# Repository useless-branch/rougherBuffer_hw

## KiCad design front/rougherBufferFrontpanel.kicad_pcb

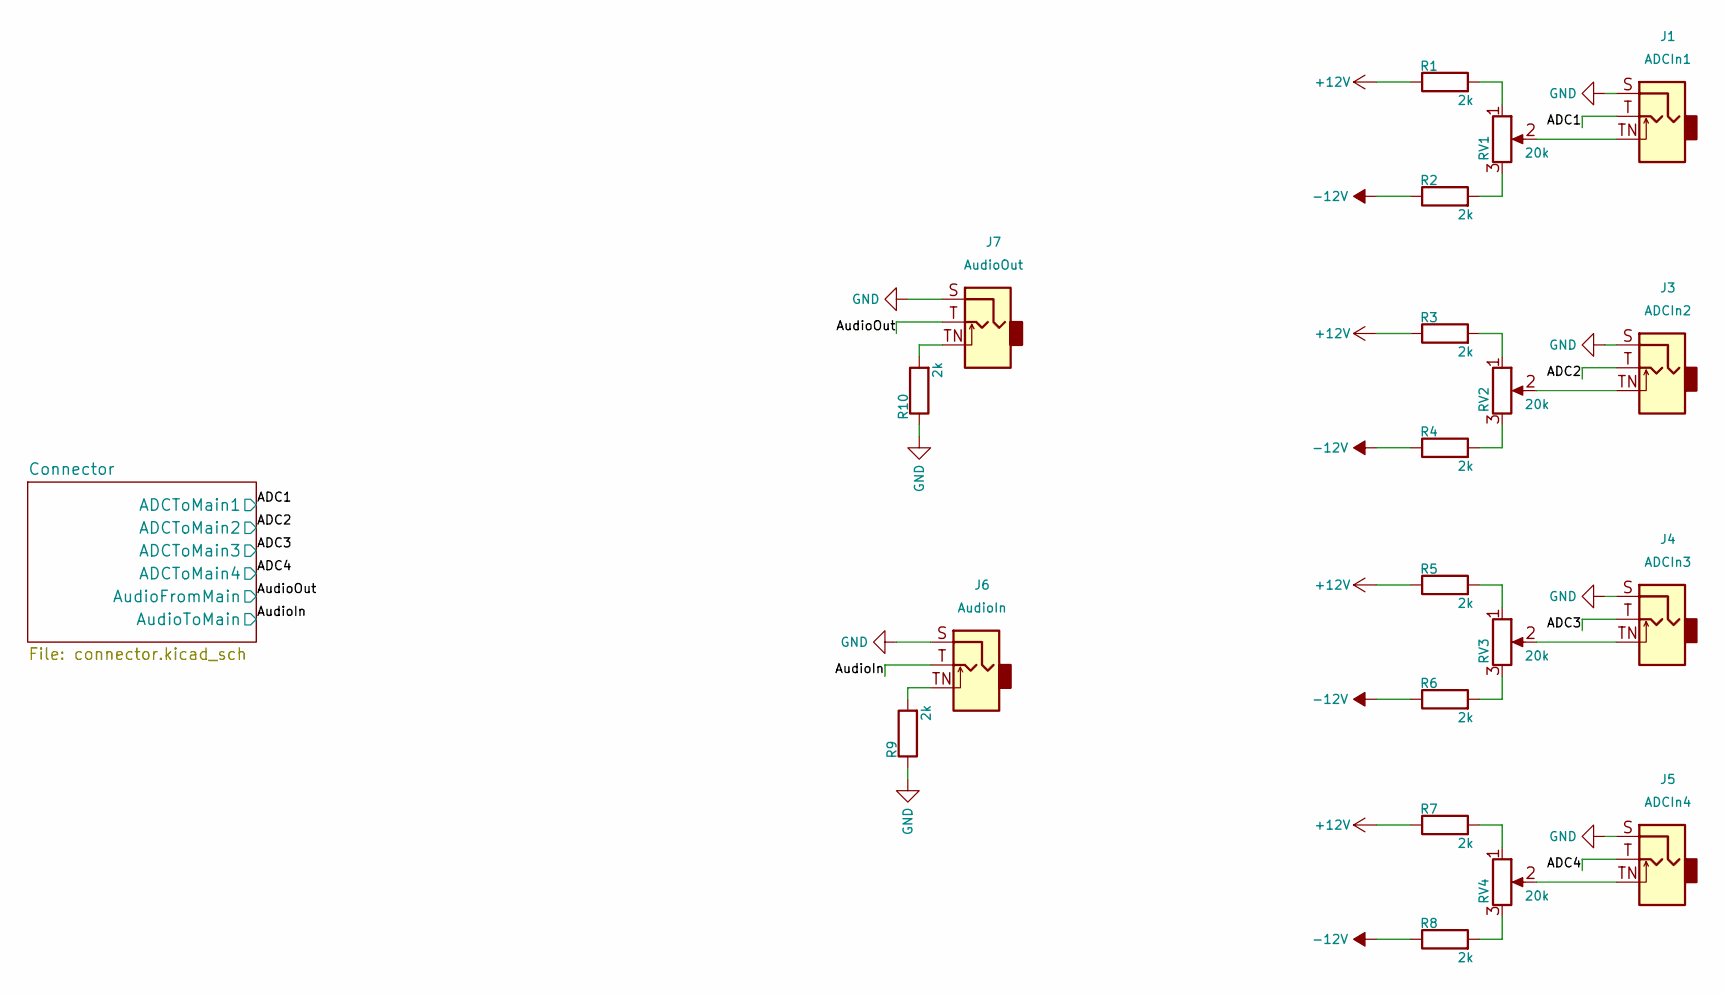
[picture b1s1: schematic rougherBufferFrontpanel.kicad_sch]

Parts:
J1: ADCIn1; Jack_3.5mm_QingPu_WQP-PJ398SM_Vertical_CircularHoles
J3: ADCIn2; Jack_3.5mm_QingPu_WQP-PJ398SM_Vertical_CircularHoles
J4: ADCIn3; Jack_3.5mm_QingPu_WQP-PJ398SM_Vertical_CircularHoles
J5: ADCIn4; Jack_3.5mm_QingPu_WQP-PJ398SM_Vertical_CircularHoles
J6: AudioIn; Jack_3.5mm_QingPu_WQP-PJ398SM_Vertical_CircularHoles
J7: AudioOut; Jack_3.5mm_QingPu_WQP-PJ398SM_Vertical_CircularHoles
R1, R2, R3, R4, R5, R6, R7, R8, R9, R10: 2k; R_0603_1608Metric
RV1, RV2, RV3, RV4: 20k; Potentiometer_Alpha_RD901F-40-00D_Single_Vertical

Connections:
+12V: R1.1, R3.1, R5.1, R7.1; also elsewhere on the board
-12V: R2.1, R4.1, R6.1, R8.1; also elsewhere on the board
/ADC1: J1.T; also elsewhere on the board
/ADC2: J3.T; also elsewhere on the board
/ADC3: J4.T; also elsewhere on the board
/ADC4: J5.T; also elsewhere on the board
/AudioIn: J6.T; also elsewhere on the board
/AudioOut: J7.T; also elsewhere on the board
GND: J1.S, J3.S, J4.S, J5.S, J6.S, J7.S, R9.1, R10.1; also elsewhere on the board
unnamed: J1.TN, RV1.2
unnamed: J3.TN, RV2.2
unnamed: J4.TN, RV3.2
unnamed: J5.TN, RV4.2
unnamed: J6.TN, R9.2
unnamed: J7.TN, R10.2
unnamed: R1.2, RV1.1
unnamed: R2.2, RV1.3
unnamed: R3.2, RV2.1
unnamed: R4.2, RV2.3
unnamed: R5.2, RV3.1
unnamed: R6.2, RV3.3
unnamed: R7.2, RV4.1
unnamed: R8.2, RV4.3

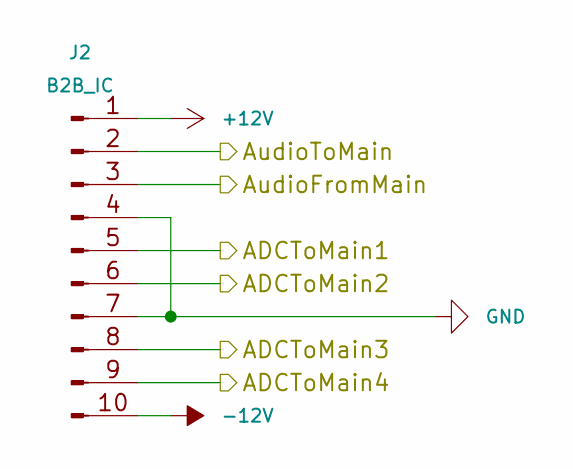
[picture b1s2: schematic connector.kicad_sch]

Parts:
J2: B2B_IC; PinHeader_1x10_P2.54mm_Vertical

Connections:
+12V: J2.1; also elsewhere on the board
-12V: J2.10; also elsewhere on the board
/ADC1: J2.5; also elsewhere on the board
/ADC2: J2.6; also elsewhere on the board
/ADC3: J2.8; also elsewhere on the board
/ADC4: J2.9; also elsewhere on the board
/AudioIn: J2.2; also elsewhere on the board
/AudioOut: J2.3; also elsewhere on the board
GND: J2.4, J2.7; also elsewhere on the board

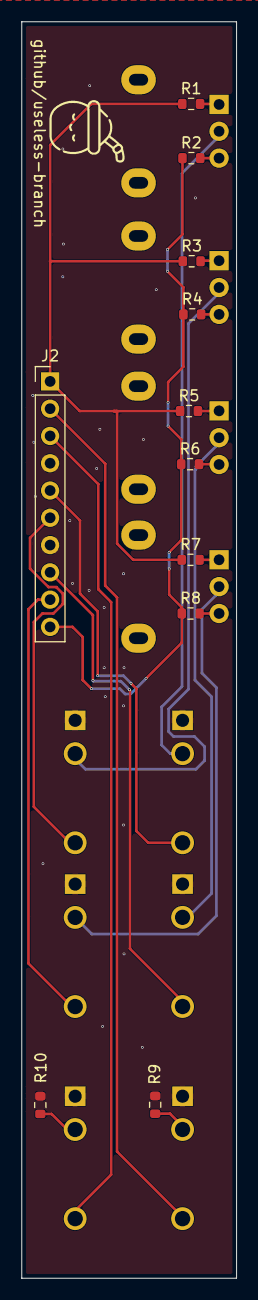
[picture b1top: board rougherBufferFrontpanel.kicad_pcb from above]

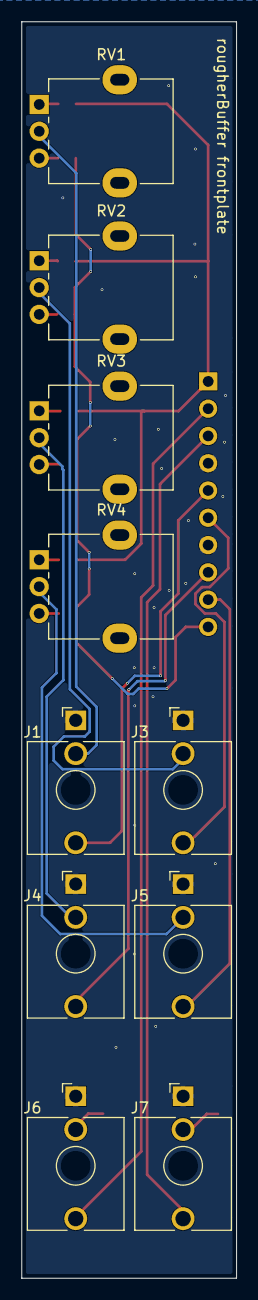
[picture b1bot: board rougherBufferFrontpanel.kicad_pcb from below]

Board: 2 copper layers, 20.0 x 117.0 mm, 21 parts (10 on the bottom side), 23 nets.

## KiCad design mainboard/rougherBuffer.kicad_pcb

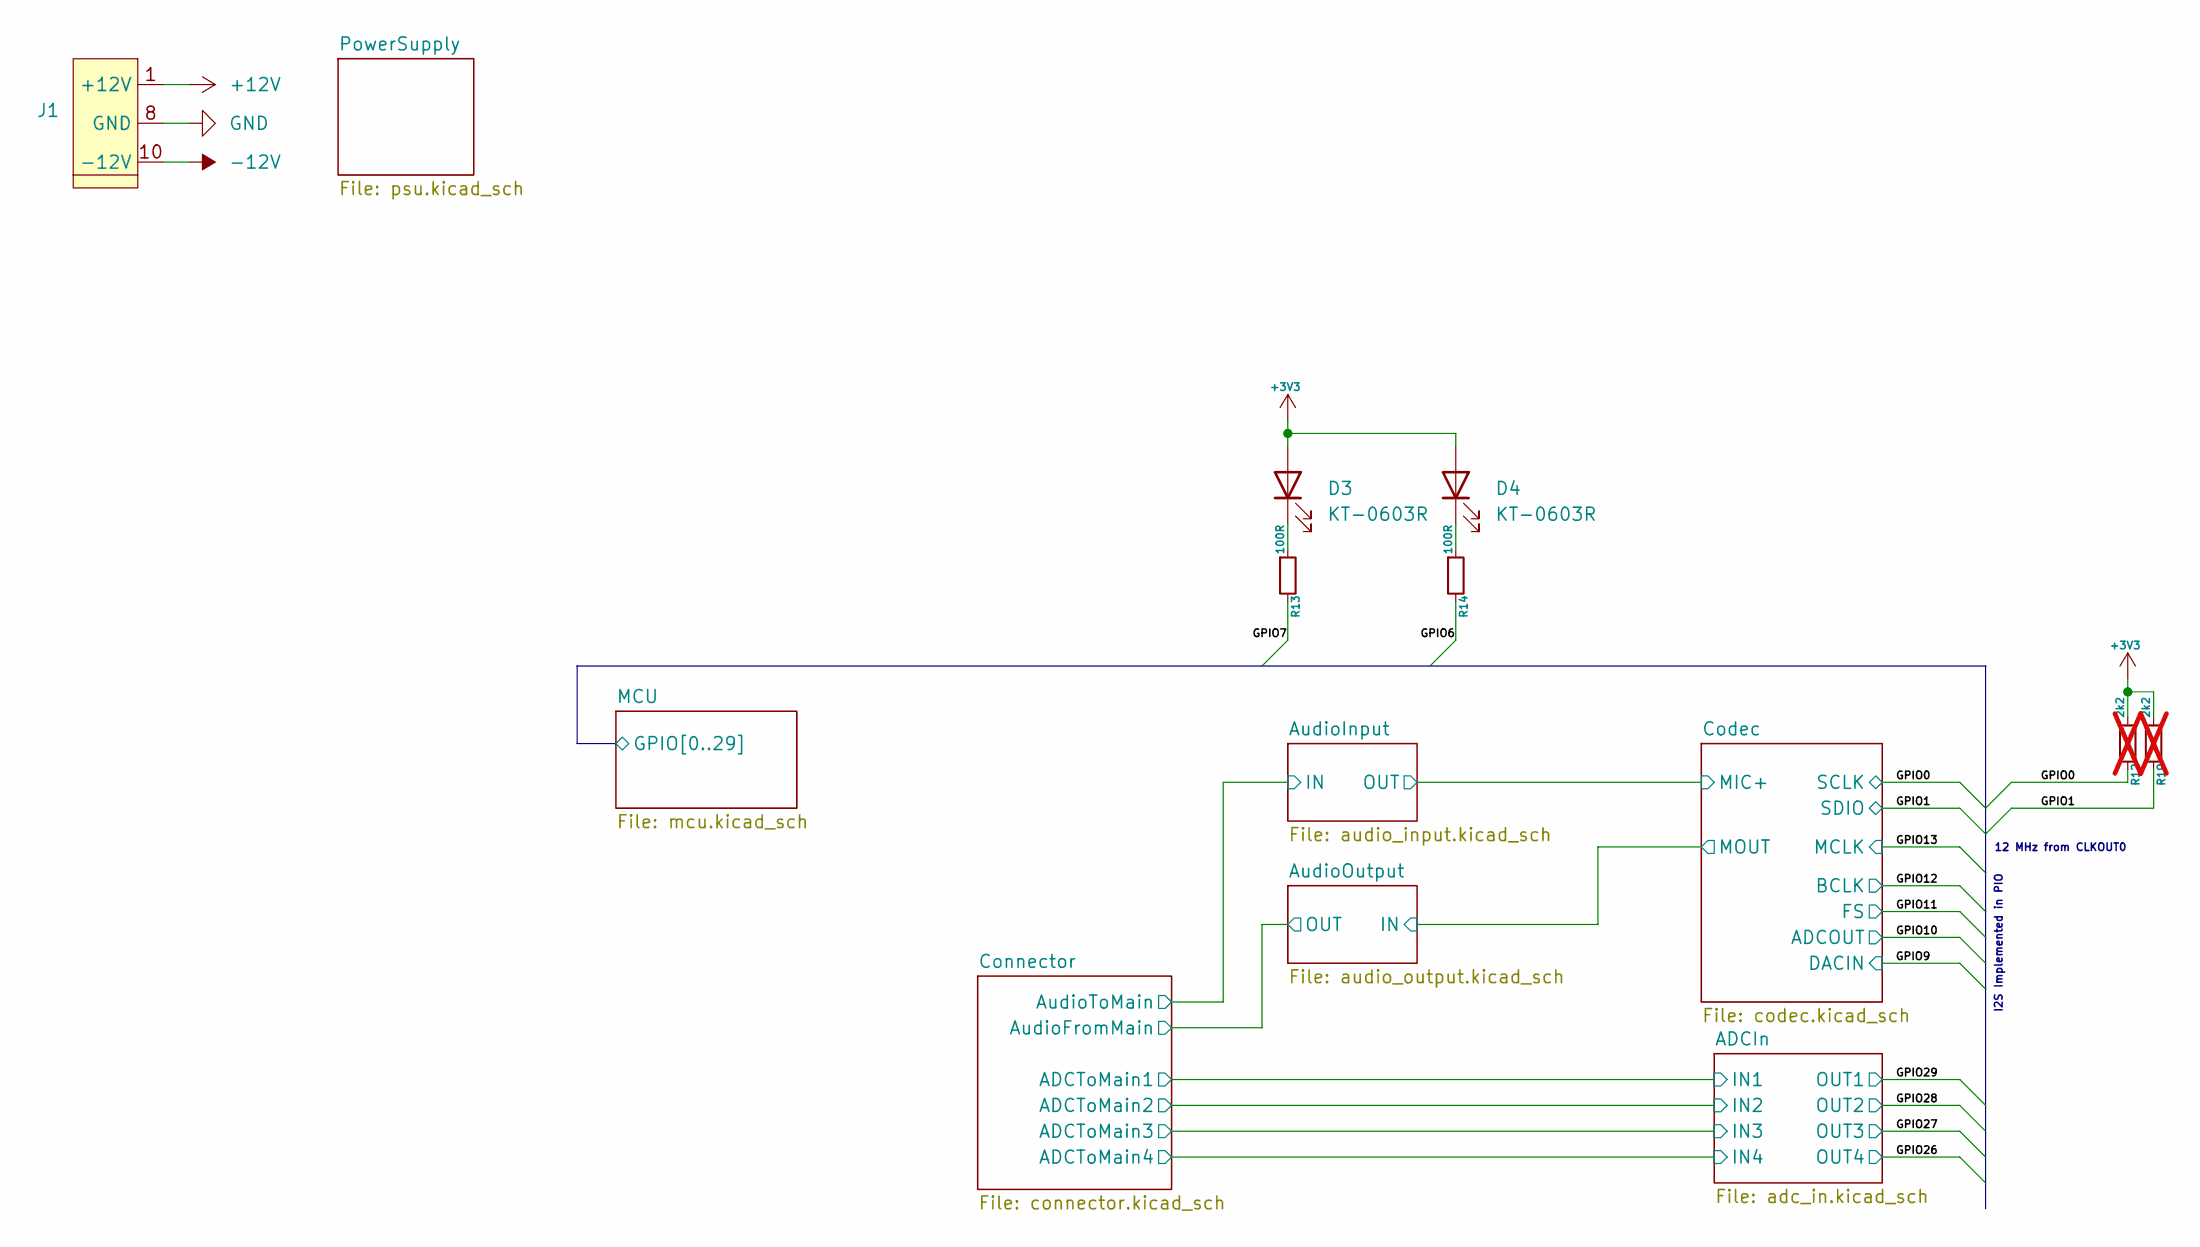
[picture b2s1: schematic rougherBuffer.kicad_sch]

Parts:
D3, D4: KT-0603R; LED_0603_1608Metric
J1: PinHeader_2x05_P2.54mm_Vertical
R12, R19: 2k2; R_0402_1005Metric; not fitted
R13, R14: 100R; R_0402_1005Metric

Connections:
+3V3: D3.2 (A), D4.2 (A), R12.1, R19.1; also elsewhere on the board
+12V: J1.1 (+12V), J1.2; also elsewhere on the board
-12V: J1.9, J1.10 (-12V); also elsewhere on the board
/MCU/GPIO0: R12.2; also elsewhere on the board
/MCU/GPIO1: R19.2; also elsewhere on the board
/MCU/GPIO6: R14.2; also elsewhere on the board
/MCU/GPIO7: R13.2; also elsewhere on the board
GND: J1.3, J1.4, J1.5, J1.6, J1.7, J1.8 (GND); also elsewhere on the board
unnamed: D3.1 (K), R13.1
unnamed: D4.1 (K), R14.1

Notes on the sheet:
12 MHz from CLKOUT0
I2S Implemented in PIO

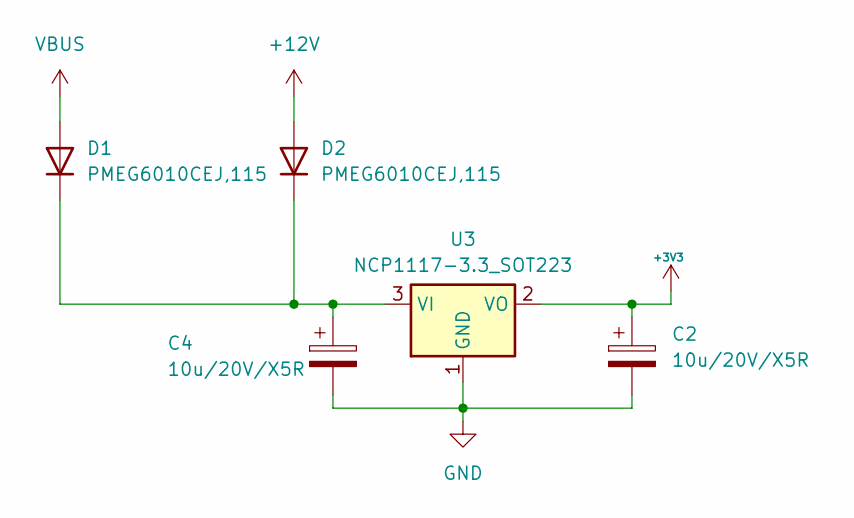
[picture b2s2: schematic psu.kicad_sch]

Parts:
C2, C4: 10u/20V/X5R; C_0805_2012Metric
D1, D2: PMEG6010CEJ,115; D_SOD-323F
U3: NCP1117-3.3_SOT223; SOT-223-3_TabPin2

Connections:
+3V3: C2.1, U3.2 (VO); also elsewhere on the board
+12V: D2.2 (A); also elsewhere on the board
GND: C2.2, C4.2, U3.1 (GND); also elsewhere on the board
unnamed: C4.1, D1.1 (K), D2.1 (K), U3.3 (VI)
VBUS: D1.2 (A); also elsewhere on the board

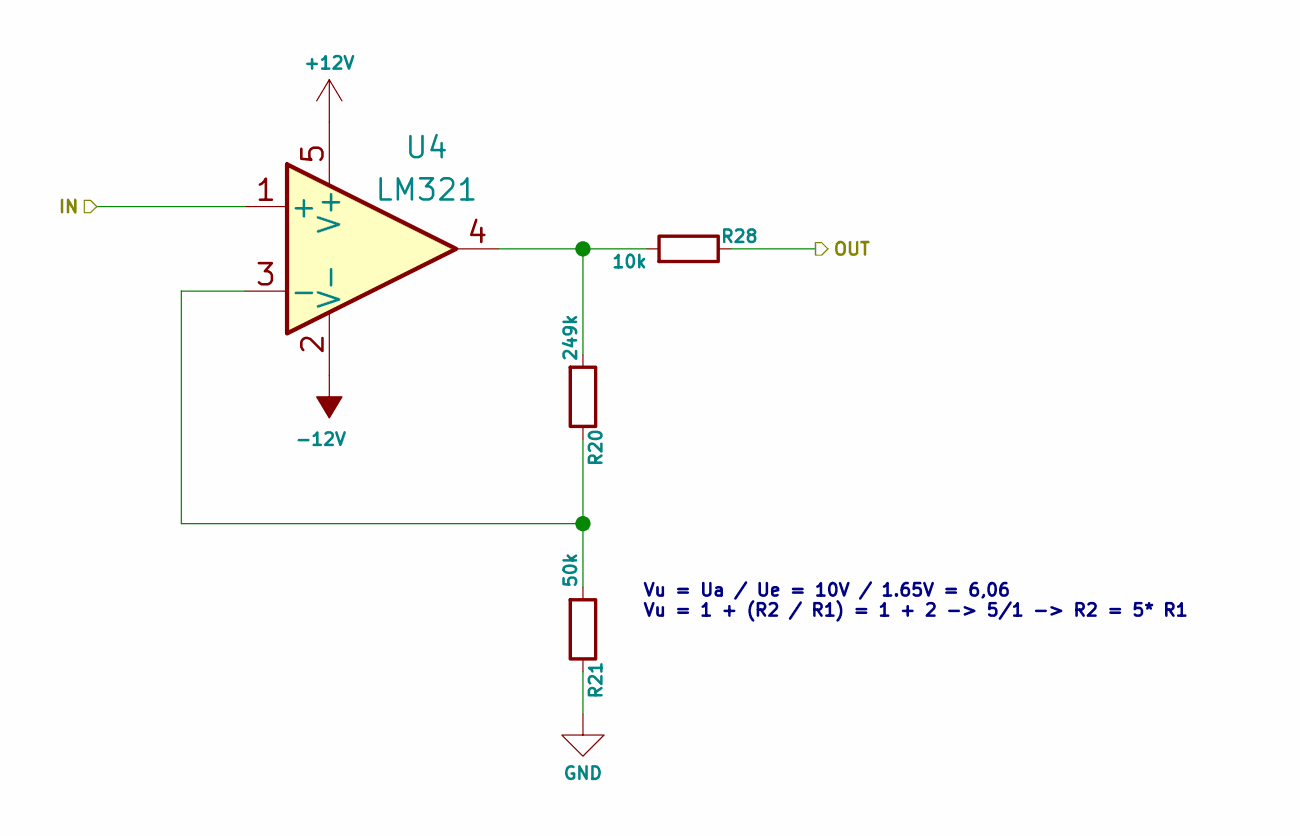
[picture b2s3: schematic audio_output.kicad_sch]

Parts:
R20: 249k; R_0402_1005Metric
R21: 50k; R_0402_1005Metric
R28: 10k; R_0402_1005Metric
U4: LM321; SOT-23-5

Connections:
+12V: U4.5 (V+); also elsewhere on the board
-12V: U4.2 (V-); also elsewhere on the board
/AudioOutput/IN: U4.1 (+); also elsewhere on the board
/AudioOutput/OUT: R28.2; also elsewhere on the board
GND: R21.2; also elsewhere on the board
unnamed: R20.1, R28.1, U4.4
unnamed: R20.2, R21.1, U4.3 (-)

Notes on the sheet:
Vu = Ua / Ue = 10V / 1.65V = 6,06 Vu = 1 + (R2 / R1) = 1 + 2 -> 5/1 -> R2 = 5* R1

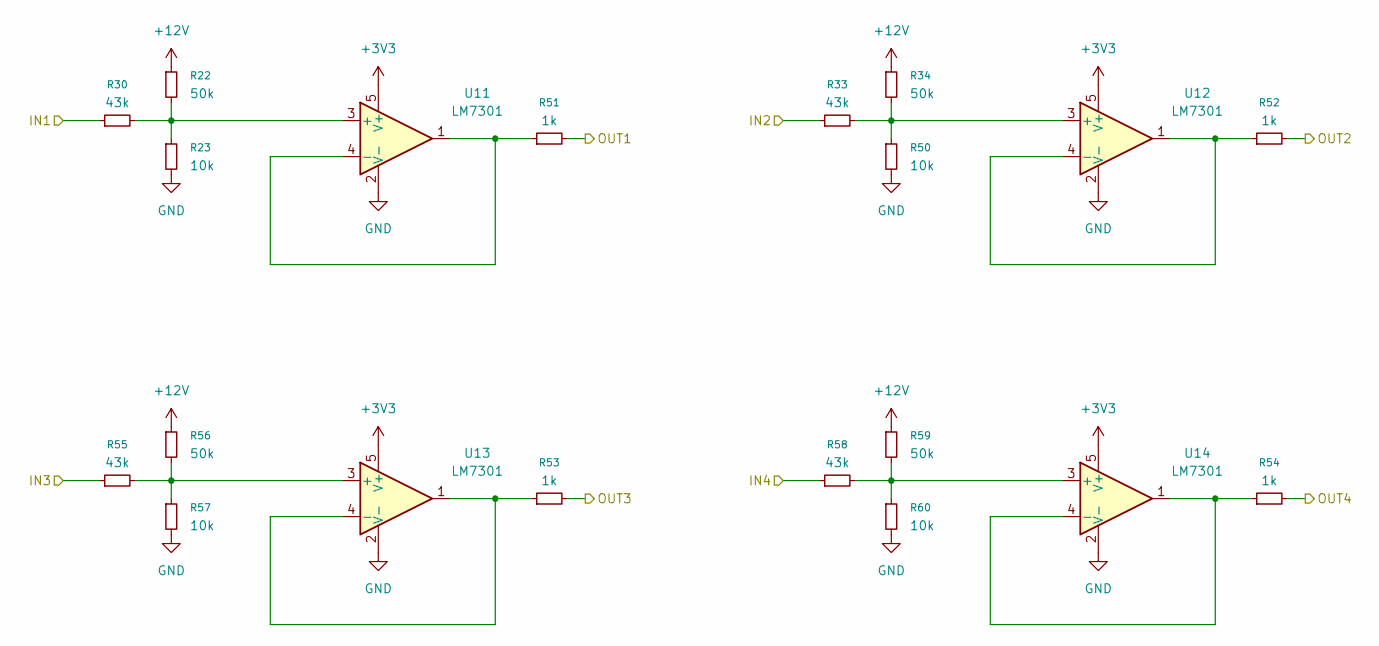
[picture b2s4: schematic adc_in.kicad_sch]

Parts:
R22, R34, R56, R59: 50k; R_0603_1608Metric
R23, R50, R57, R60: 10k; R_0603_1608Metric
R30, R33, R55, R58: 43k; R_0603_1608Metric
R51, R52, R53, R54: 1k; R_0603_1608Metric
U11, U12, U13, U14: LM7301; SOT-23-5

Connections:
+3V3: U11.5 (V+), U12.5 (V+), U13.5 (V+), U14.5 (V+); also elsewhere on the board
+12V: R22.1, R34.1, R56.1, R59.1; also elsewhere on the board
/ADCIn/IN1: R30.1; also elsewhere on the board
/ADCIn/IN2: R33.1; also elsewhere on the board
/ADCIn/IN3: R55.1; also elsewhere on the board
/ADCIn/IN4: R58.1; also elsewhere on the board
/MCU/GPIO26: R54.2; also elsewhere on the board
/MCU/GPIO27: R53.2; also elsewhere on the board
/MCU/GPIO28: R52.2; also elsewhere on the board
/MCU/GPIO29: R51.2; also elsewhere on the board
GND: R23.2, R50.2, R57.2, R60.2, U11.2 (V-), U12.2 (V-), U13.2 (V-), U14.2 (V-); also elsewhere on the board
unnamed: R22.2, R23.1, R30.2, U11.3 (+)
unnamed: R51.1, U11.1, U11.4 (-)
unnamed: R33.2, R34.2, R50.1, U12.3 (+)
unnamed: R52.1, U12.1, U12.4 (-)
unnamed: R55.2, R56.2, R57.1, U13.3 (+)
unnamed: R53.1, U13.1, U13.4 (-)
unnamed: R58.2, R59.2, R60.1, U14.3 (+)
unnamed: R54.1, U14.1, U14.4 (-)

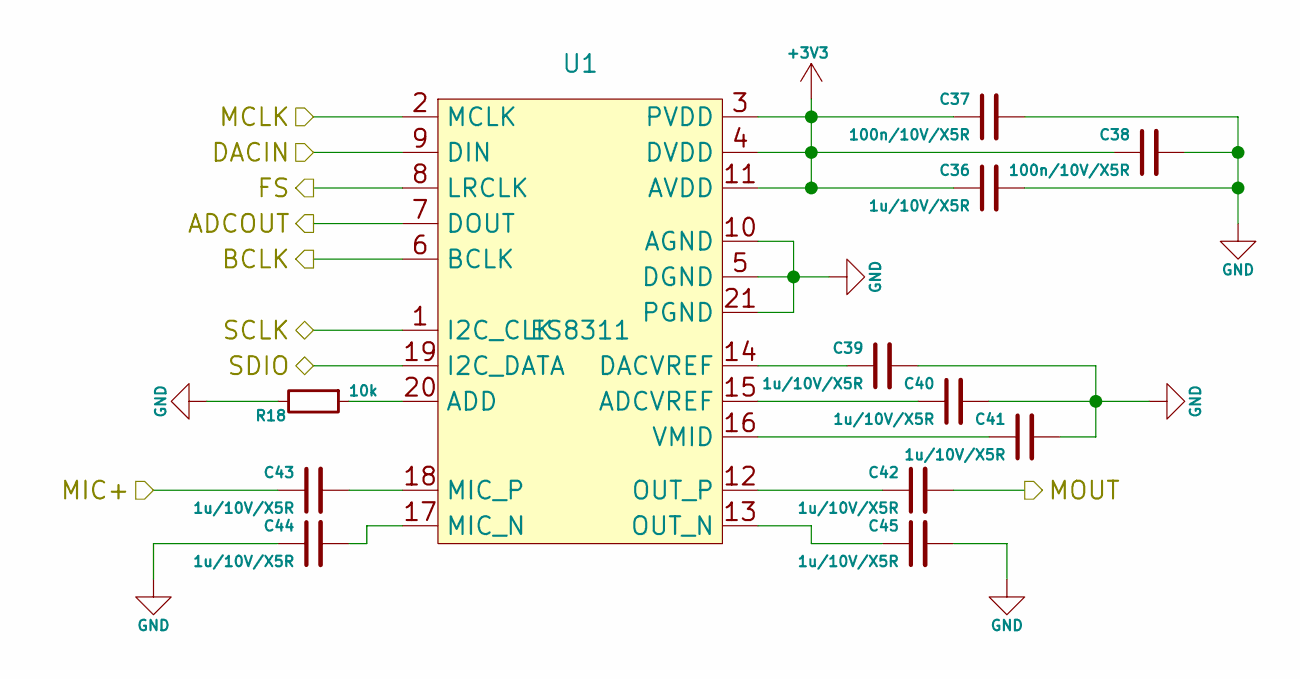
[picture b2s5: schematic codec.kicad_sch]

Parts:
C36, C39, C40, C41, C42, C43, C44, C45: 1u/10V/X5R; C_0603_1608Metric
C37, C38: 100n/10V/X5R; C_0402_1005Metric
R18: 10k; R_0402_1005Metric
U1: ES8311; QFN-20-1EP_3x3mm_P0.45mm_EP1.6x1.6mm

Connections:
+3V3: C36.1, C37.1, C38.1, U1.3 (PVDD), U1.4 (DVDD), U1.11 (AVDD); also elsewhere on the board
/AudioInput/OUT: C43.1; also elsewhere on the board
/AudioOutput/IN: C42.2; also elsewhere on the board
/MCU/GPIO0: U1.1 (I2C_CLK); also elsewhere on the board
/MCU/GPIO1: U1.19 (I2C_DATA); also elsewhere on the board
/MCU/GPIO9: U1.9 (DIN); also elsewhere on the board
/MCU/GPIO10: U1.7 (DOUT); also elsewhere on the board
/MCU/GPIO11: U1.8 (LRCLK); also elsewhere on the board
/MCU/GPIO12: U1.6 (BCLK); also elsewhere on the board
/MCU/GPIO13: U1.2 (MCLK); also elsewhere on the board
GND: C36.2, C37.2, C38.2, C39.2, C40.2, C41.2, C44.1, C45.2, R18.2, U1.5 (DGND), U1.10 (AGND), U1.21 (PGND); also elsewhere on the board
unnamed: C40.1, U1.15 (ADCVREF)
unnamed: R18.1, U1.20 (ADD)
unnamed: C39.1, U1.14 (DACVREF)
unnamed: C44.2, U1.17 (MIC_N)
unnamed: C43.2, U1.18 (MIC_P)
unnamed: C45.1, U1.13 (OUT_N)
unnamed: C42.1, U1.12 (OUT_P)
unnamed: C41.1, U1.16 (VMID)

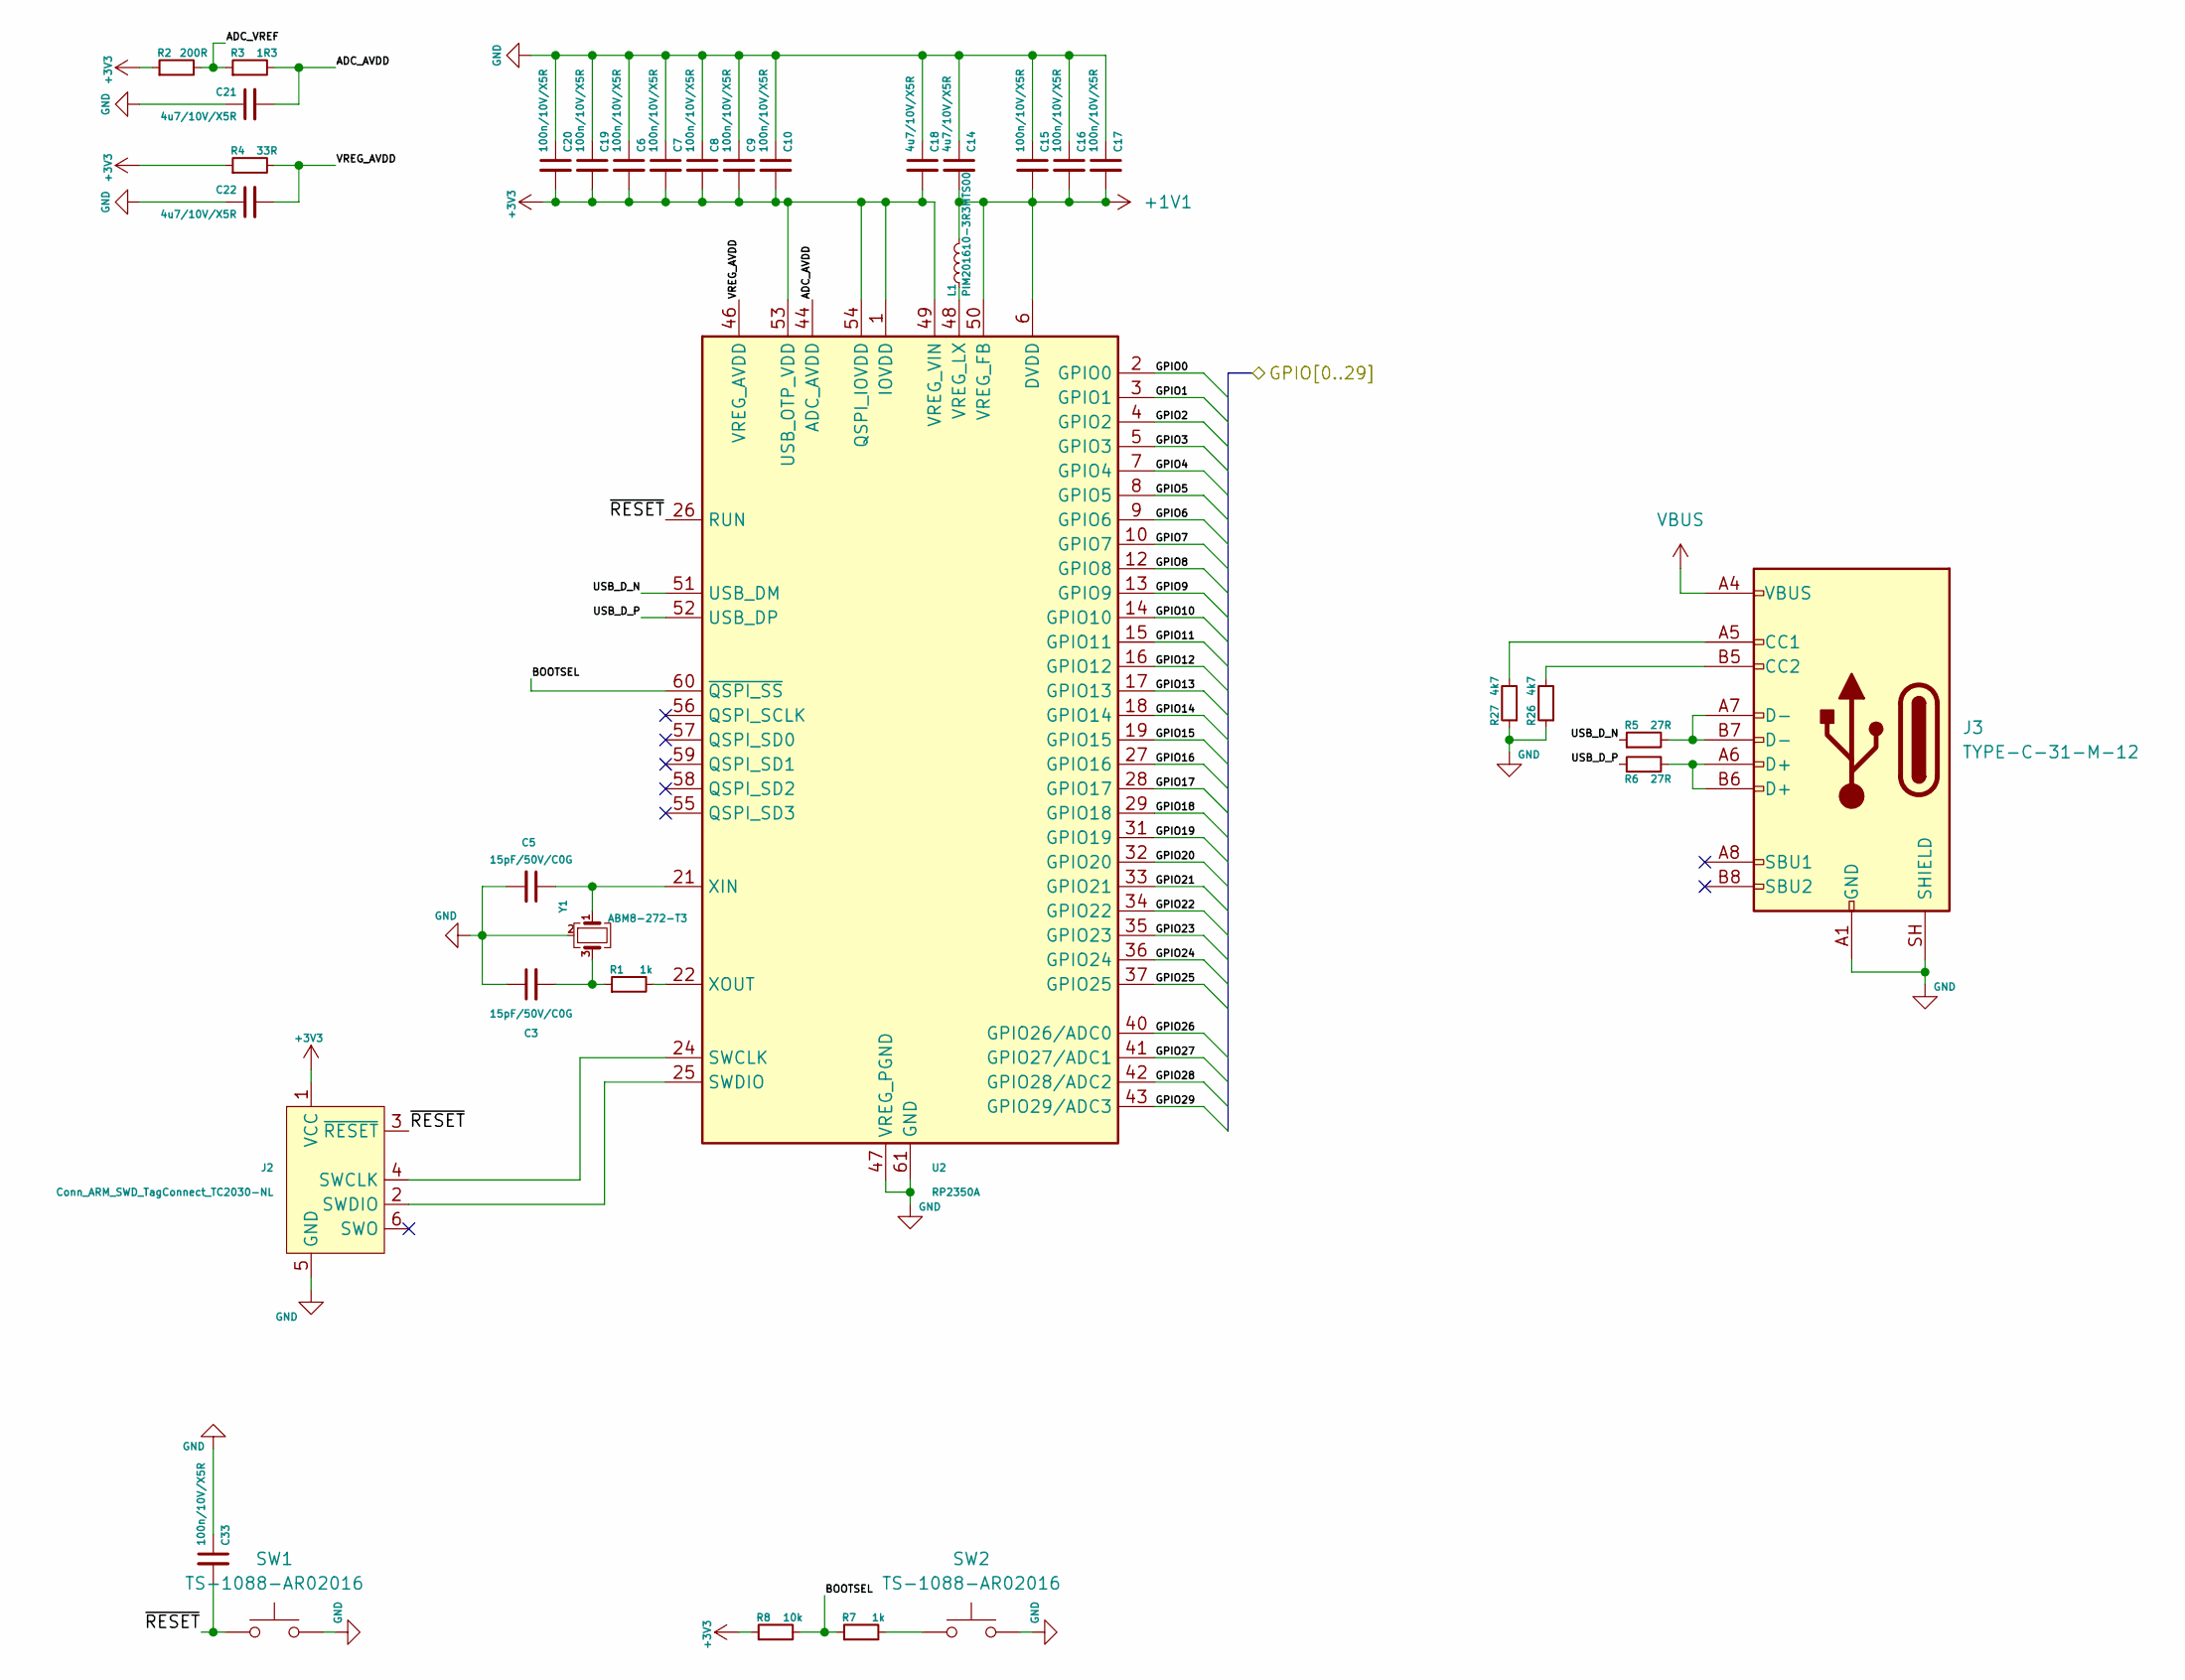
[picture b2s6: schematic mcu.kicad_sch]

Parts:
C3, C5: 15pF/50V/C0G; C_0402_1005Metric
C6, C7, C8, C9, C10, C15, C17, C19, C20, C33: 100n/10V/X5R; C_0402_1005Metric
C14, C18, C21, C22: 4u7/10V/X5R; C_0603_1608Metric
C16: 100n/10V/X5R; C_0603_1608Metric
J2: Conn_ARM_SWD_TagConnect_TC2030-NL; Tag-Connect_TC2030-IDC-NL_2x03_P1.27mm_Vertical
J3: TYPE-C-31-M-12; USB_C_Receptacle_G-Switch_GT-USB-7010ASV
L1: PIM201610-3R3MTS00; L_Changjiang_FTC201610D
R1, R7: 1k; R_0402_1005Metric
R2: 200R; R_0402_1005Metric
R3: 1R3; R_0402_1005Metric
R4: 33R; R_0402_1005Metric
R5, R6: 27R; R_0402_1005Metric
R8: 10k; R_0402_1005Metric
R26, R27: 4k7; R_0402_1005Metric
SW1, SW2: TS-1088-AR02016; SW_SPST_TS-1088-xR025
U2: RP2350A; QFN-60-1EP_7x7mm_P0.4mm_EP3.4x3.4mm
Y1: ABM8-272-T3; Crystal_SMD_Abracon_ABM8AIG-4Pin_3.2x2.5mm

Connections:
+1V1: C14.2, C15.2, C16.2, C17.2, L1.2, U2.6 (DVDD), U2.23 (DVDD), U2.39 (DVDD), U2.50 (VREG_FB)
+3V3: C6.2, C7.2, C8.2, C9.2, C10.2, C18.2, C19.2, C20.2, J2.1 (VCC), R2.1, R4.1, R8.1, U2.1 (IOVDD), U2.11 (IOVDD), U2.20 (IOVDD), U2.30 (IOVDD), U2.38 (IOVDD), U2.45 (IOVDD), U2.49 (VREG_VIN), U2.53 (USB_OTP_VDD), U2.54 (QSPI_IOVDD); also elsewhere on the board
/MCU/ADC_AVDD: C21.2, R3.2, U2.44 (ADC_AVDD)
/MCU/ADC_VREF: R2.2, R3.1
/MCU/BOOTSEL: R7.1, R8.2, U2.60 (~QSPI_SS)
/MCU/GPIO0: U2.2 (GPIO0); also elsewhere on the board
/MCU/GPIO1: U2.3 (GPIO1); also elsewhere on the board
/MCU/GPIO2: U2.4 (GPIO2)
/MCU/GPIO3: U2.5 (GPIO3)
/MCU/GPIO4: U2.7 (GPIO4)
/MCU/GPIO5: U2.8 (GPIO5)
/MCU/GPIO6: U2.9 (GPIO6); also elsewhere on the board
/MCU/GPIO7: U2.10 (GPIO7); also elsewhere on the board
/MCU/GPIO8: U2.12 (GPIO8)
/MCU/GPIO9: U2.13 (GPIO9); also elsewhere on the board
/MCU/GPIO10: U2.14 (GPIO10); also elsewhere on the board
/MCU/GPIO11: U2.15 (GPIO11); also elsewhere on the board
/MCU/GPIO12: U2.16 (GPIO12); also elsewhere on the board
/MCU/GPIO13: U2.17 (GPIO13); also elsewhere on the board
/MCU/GPIO14: U2.18 (GPIO14)
/MCU/GPIO15: U2.19 (GPIO15)
/MCU/GPIO16: U2.27 (GPIO16)
/MCU/GPIO17: U2.28 (GPIO17)
/MCU/GPIO18: U2.29 (GPIO18)
/MCU/GPIO19: U2.31 (GPIO19)
/MCU/GPIO20: U2.32 (GPIO20)
/MCU/GPIO21: U2.33 (GPIO21)
/MCU/GPIO22: U2.34 (GPIO22)
/MCU/GPIO23: U2.35 (GPIO23)
/MCU/GPIO24: U2.36 (GPIO24)
/MCU/GPIO25: U2.37 (GPIO25)
/MCU/GPIO26: U2.40 (GPIO26/ADC0); also elsewhere on the board
/MCU/GPIO27: U2.41 (GPIO27/ADC1); also elsewhere on the board
/MCU/GPIO28: U2.42 (GPIO28/ADC2); also elsewhere on the board
/MCU/GPIO29: U2.43 (GPIO29/ADC3); also elsewhere on the board
/MCU/USB_D_N: R5.1, U2.51 (USB_DM)
/MCU/USB_D_P: R6.1, U2.52 (USB_DP)
/MCU/VREG_AVDD: C22.2, R4.2, U2.46 (VREG_AVDD)
/MCU/~RESET: C33.2, J2.3 (~RESET), SW1.1, U2.26 (RUN)
GND: C3.1, C5.2, C6.1, C7.1, C8.1, C9.1, C10.1, C14.1, C15.1, C16.1, C17.1, C18.1, C19.1, C20.1, C21.1, C22.1, C33.1, J2.5 (GND), J3.A1 (GND), J3.A12 (GND), J3.B1 (GND), J3.B12 (GND), J3.SH (SHIELD), R26.1, R27.1, SW1.2, SW2.2, U2.47 (VREG_PGND), U2.61 (GND), Y1.2 (G), Y1.4 (G); also elsewhere on the board
unnamed: C3.2, R1.1, Y1.3
unnamed: J2.4 (SWCLK), U2.24 (SWCLK)
unnamed: J2.2 (SWDIO), U2.25 (SWDIO)
unnamed: J3.A5 (CC1), R27.2
unnamed: J3.B5 (CC2), R26.2
unnamed: J3.A6 (D+), J3.B6 (D+), R6.2
unnamed: J3.A7 (D-), J3.B7 (D-), R5.2
unnamed: R7.2, SW2.1
unnamed: L1.1, U2.48 (VREG_LX)
unnamed: C5.1, U2.21 (XIN), Y1.1
unnamed: R1.2, U2.22 (XOUT)
VBUS: J3.A4 (VBUS), J3.A9 (VBUS), J3.B4 (VBUS), J3.B9 (VBUS); also elsewhere on the board

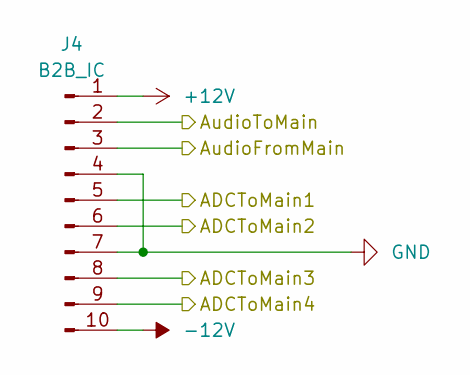
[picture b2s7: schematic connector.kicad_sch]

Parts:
J4: B2B_IC; PinHeader_1x10_P2.54mm_Horizontal

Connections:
+12V: J4.1; also elsewhere on the board
-12V: J4.10; also elsewhere on the board
/ADCIn/IN1: J4.5; also elsewhere on the board
/ADCIn/IN2: J4.6; also elsewhere on the board
/ADCIn/IN3: J4.8; also elsewhere on the board
/ADCIn/IN4: J4.9; also elsewhere on the board
/AudioInput/IN: J4.2; also elsewhere on the board
/AudioOutput/OUT: J4.3; also elsewhere on the board
GND: J4.4, J4.7; also elsewhere on the board

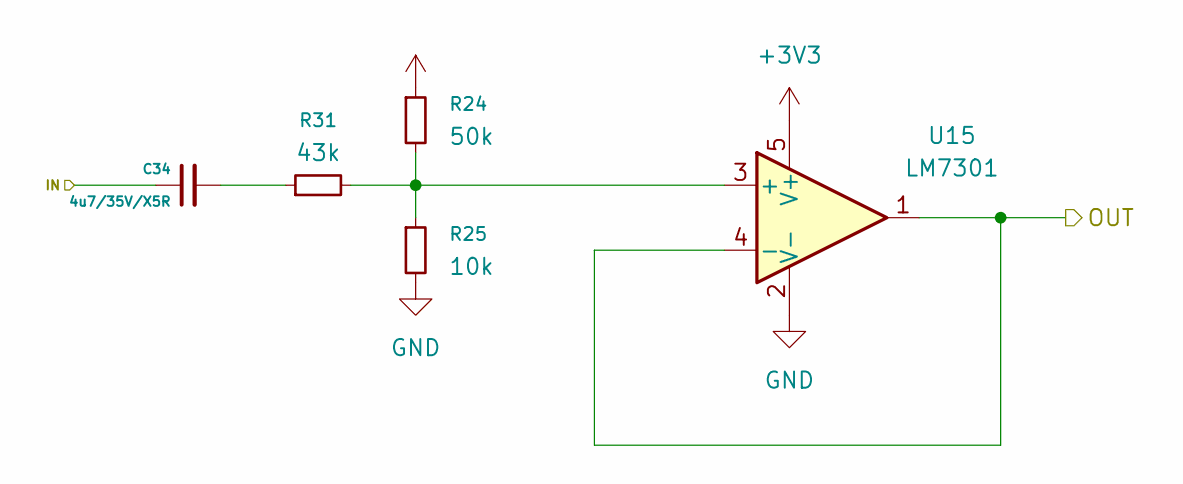
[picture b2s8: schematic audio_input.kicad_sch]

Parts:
C34: 4u7/35V/X5R; C_0603_1608Metric
R24: 50k; R_0603_1608Metric
R25: 10k; R_0603_1608Metric
R31: 43k; R_0603_1608Metric
U15: LM7301; SOT-23-5

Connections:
+3V3: U15.5 (V+); also elsewhere on the board
+12V: R24.1; also elsewhere on the board
/AudioInput/IN: C34.1; also elsewhere on the board
/AudioInput/OUT: U15.1, U15.4 (-); also elsewhere on the board
GND: R25.2, U15.2 (V-); also elsewhere on the board
unnamed: C34.2, R31.1
unnamed: R24.2, R25.1, R31.2, U15.3 (+)

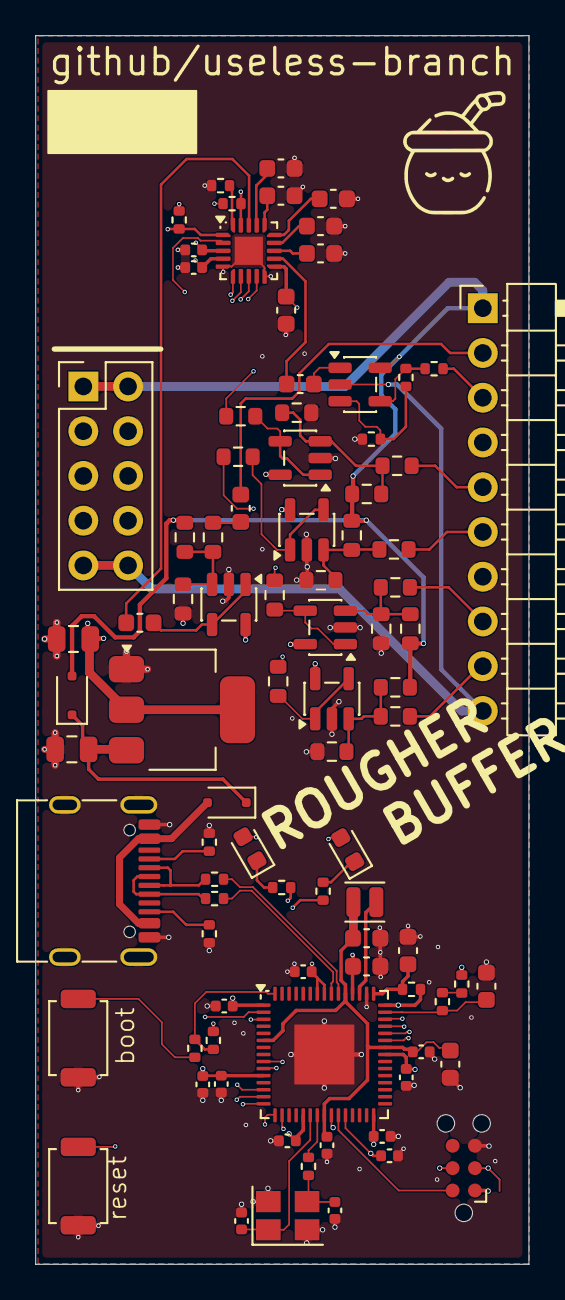
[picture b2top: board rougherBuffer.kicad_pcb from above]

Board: 4 copper layers, 28.0 x 69.7 mm, 88 parts (0 on the bottom side), 68 nets.
